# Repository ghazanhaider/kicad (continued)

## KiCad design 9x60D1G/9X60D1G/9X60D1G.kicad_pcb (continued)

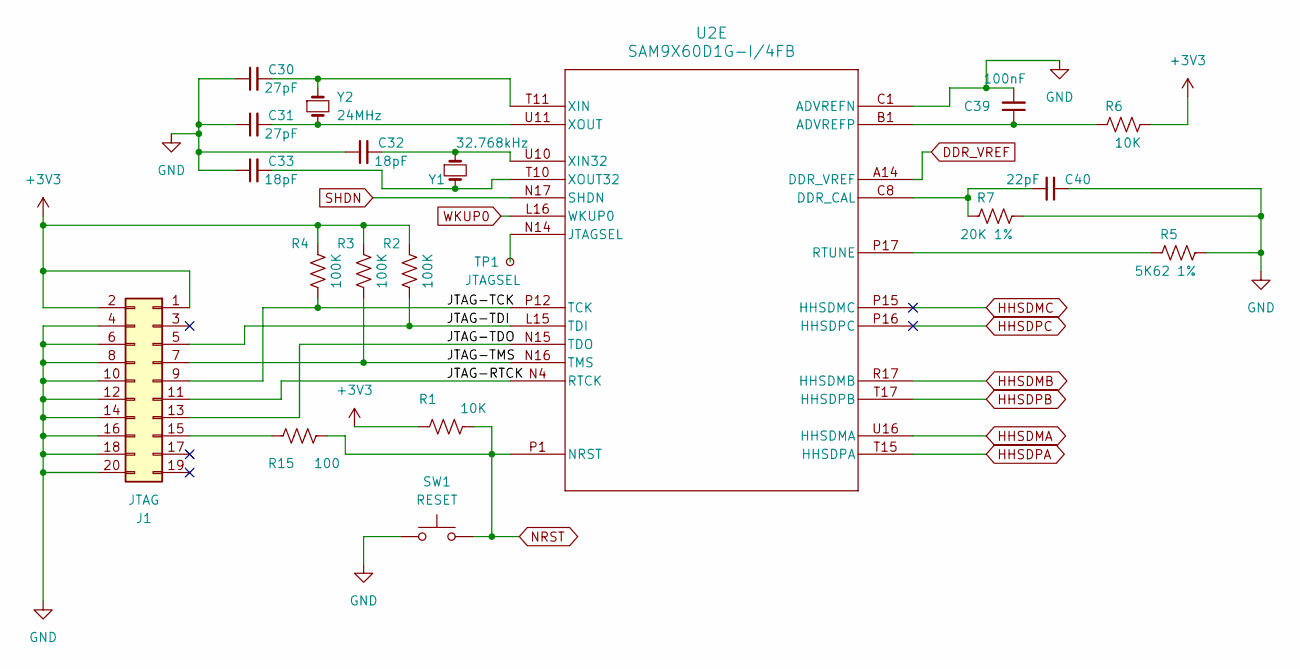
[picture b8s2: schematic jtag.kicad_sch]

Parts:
C30, C31: 27pF; C_0805_2012Metric
C32, C33: 18pF; C_0805_2012Metric
C39: 100nF; C_0805_2012Metric
C40: 22pF; C_0402_1005Metric
J1: JTAG; PinHeader_2x10_P2.54mm_Vertical
R1, R6: 10K; R_0805_2012Metric
R2, R3, R4: 100K; R_0805_2012Metric
R5: 5K62 1%; R_0402_1005Metric
R7: 20K 1%; R_0402_1005Metric
R15: 100; R_0805_2012Metric
SW1: RESET; SW_Push_1P1T_NO_6x6mm_H9.5mm
TP1: JTAGSEL; TestPoint_Pad_D1.0mm
U2: SAM9X60D1G-I/4FB; 233TFBGA_MCH
Y1: 32.768kHz; Crystal_SMD_3215-2Pin_3.2x1.5mm
Y2: 24MHz; Crystal_SMD_5032-2Pin_5.0x3.2mm

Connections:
+3V3: J1.1, J1.2, R1.1, R2.1, R3.1, R4.1, R6.2; also elsewhere on the board
/JTAG/JTAG-RTCK: J1.11, U2.N4 (RTCK)
/JTAG/JTAG-TCK: J1.9, R4.2, U2.P12 (TCK)
/JTAG/JTAG-TDI: J1.5, R2.2, U2.L15 (TDI)
/JTAG/JTAG-TDO: J1.13, U2.N15 (TDO)
/JTAG/JTAG-TMS: J1.7, R3.2, U2.N16 (TMS)
DDR_VREF: U2.A14 (DDR_VREF); also elsewhere on the board
GND: C30.1, C31.1, C32.1, C33.1, C39.2, C40.1, J1.4, J1.6, J1.8, J1.10, J1.12, J1.14, J1.16, J1.18, J1.20, R5.2, R7.2, SW1.1, U2.C1 (ADVREFN); also elsewhere on the board
HHSDMA: U2.U16 (HHSDMA); also elsewhere on the board
HHSDMB: U2.R17 (HHSDMB); also elsewhere on the board
HHSDMC: U2.P15 (HHSDMC)
HHSDPA: U2.T15 (HHSDPA); also elsewhere on the board
HHSDPB: U2.T17 (HHSDPB); also elsewhere on the board
HHSDPC: U2.P16 (HHSDPC)
NRST: R1.2, R15.2, SW1.2, U2.P1 (NRST); also elsewhere on the board
unnamed: J1.15, R15.1
unnamed: C39.1, R6.1, U2.B1 (ADVREFP)
unnamed: C40.2, R7.1, U2.C8 (DDR_CAL)
unnamed: TP1.1, U2.N14 (JTAGSEL)
unnamed: R5.1, U2.P17 (RTUNE)
unnamed: C32.2, U2.U10 (XIN32), Y1.1
unnamed: C30.2, U2.T11 (XIN), Y2.1
unnamed: C33.2, U2.T10 (XOUT32), Y1.2
unnamed: C31.2, U2.U11 (XOUT), Y2.2
SHDN: U2.N17 (SHDN); also elsewhere on the board
WKUP0: U2.L16 (WKUP0); also elsewhere on the board

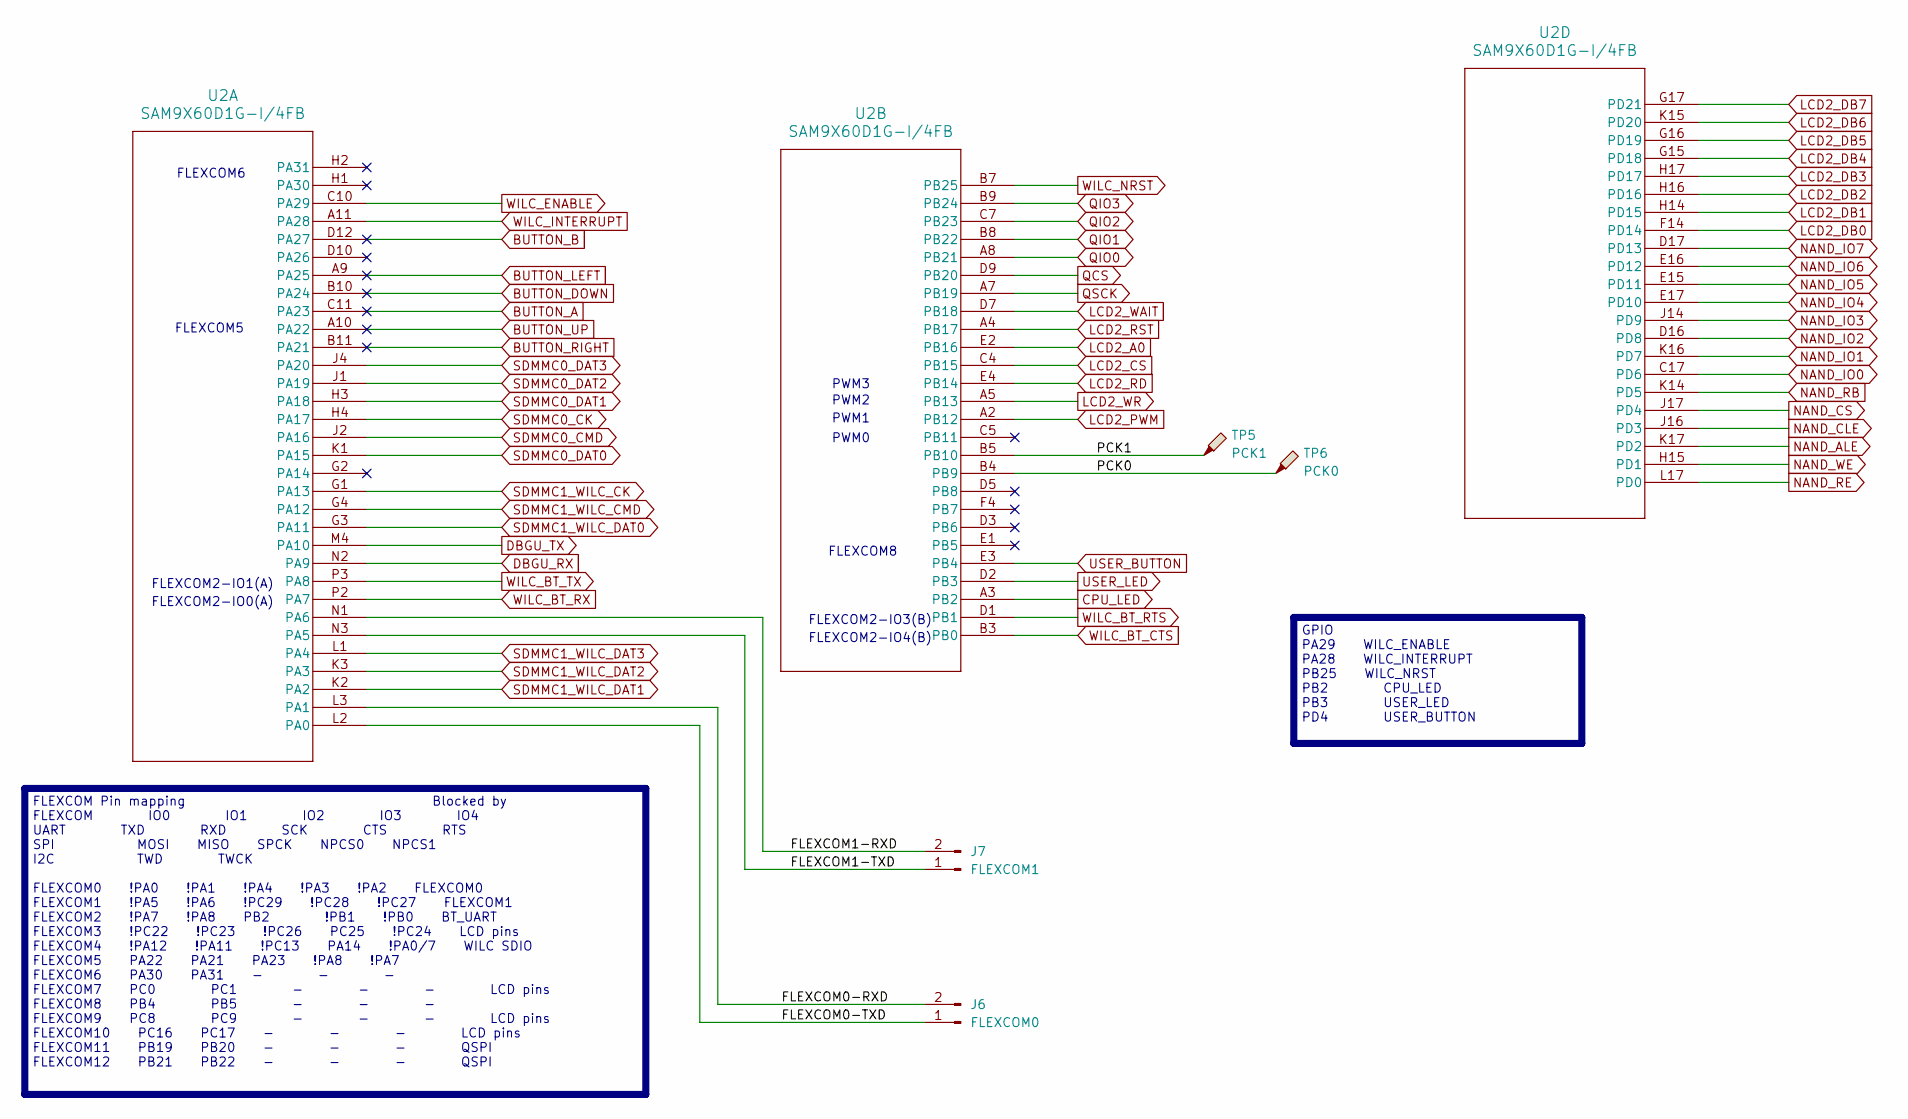
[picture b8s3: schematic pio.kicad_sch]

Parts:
J6: FLEXCOM0; PinHeader_1x02_P2.54mm_Vertical
J7: FLEXCOM1; PinHeader_1x02_P2.54mm_Vertical
TP5: PCK1; TestPoint_Pad_D1.0mm
TP6: PCK0; TestPoint_Pad_D1.0mm
U2: SAM9X60D1G-I/4FB; 233TFBGA_MCH

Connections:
/PIO breakout/FLEXCOM0-RXD: J6.2, U2.L3 (PA1)
/PIO breakout/FLEXCOM0-TXD: J6.1, U2.L2 (PA0)
/PIO breakout/FLEXCOM1-RXD: J7.2, U2.N1 (PA6)
/PIO breakout/FLEXCOM1-TXD: J7.1, U2.N3 (PA5)
/PIO breakout/PCK0: TP6.1, U2.B4 (PB9)
/PIO breakout/PCK1: TP5.1, U2.B5 (PB10)
BUTTON_A: U2.C11 (PA23); also elsewhere on the board
BUTTON_B: U2.D12 (PA27); also elsewhere on the board
BUTTON_DOWN: U2.B10 (PA24); also elsewhere on the board
BUTTON_LEFT: U2.A9 (PA25); also elsewhere on the board
BUTTON_RIGHT: U2.B11 (PA21); also elsewhere on the board
BUTTON_UP: U2.A10 (PA22); also elsewhere on the board
CPU_LED: U2.A3 (PB2); also elsewhere on the board
DBGU_RX: U2.N2 (PA9); also elsewhere on the board
DBGU_TX: U2.M4 (PA10); also elsewhere on the board
LCD2_A0: U2.E2 (PB16); also elsewhere on the board
LCD2_CS: U2.C4 (PB15); also elsewhere on the board
LCD2_DB0: U2.F14 (PD14); also elsewhere on the board
LCD2_DB1: U2.H14 (PD15); also elsewhere on the board
LCD2_DB2: U2.H16 (PD16); also elsewhere on the board
LCD2_DB3: U2.H17 (PD17); also elsewhere on the board
LCD2_DB4: U2.G15 (PD18); also elsewhere on the board
LCD2_DB5: U2.G16 (PD19); also elsewhere on the board
LCD2_DB6: U2.K15 (PD20); also elsewhere on the board
LCD2_DB7: U2.G17 (PD21); also elsewhere on the board
LCD2_PWM: U2.A2 (PB12); also elsewhere on the board
LCD2_RD: U2.E4 (PB14); also elsewhere on the board
LCD2_RST: U2.A4 (PB17); also elsewhere on the board
LCD2_WAIT: U2.D7 (PB18); also elsewhere on the board
LCD2_WR: U2.A5 (PB13); also elsewhere on the board
NAND_ALE: U2.K17 (PD2); also elsewhere on the board
NAND_CLE: U2.J16 (PD3); also elsewhere on the board
NAND_CS: U2.J17 (PD4); also elsewhere on the board
NAND_IO0: U2.C17 (PD6); also elsewhere on the board
NAND_IO1: U2.K16 (PD7); also elsewhere on the board
NAND_IO2: U2.D16 (PD8); also elsewhere on the board
NAND_IO3: U2.J14 (PD9); also elsewhere on the board
NAND_IO4: U2.E17 (PD10); also elsewhere on the board
NAND_IO5: U2.E15 (PD11); also elsewhere on the board
NAND_IO6: U2.E16 (PD12); also elsewhere on the board
NAND_IO7: U2.D17 (PD13); also elsewhere on the board
NAND_RB: U2.K14 (PD5); also elsewhere on the board
NAND_RE: U2.L17 (PD0); also elsewhere on the board
NAND_WE: U2.H15 (PD1); also elsewhere on the board
QCS: U2.D9 (PB20); also elsewhere on the board
QIO0: U2.A8 (PB21); also elsewhere on the board
QIO1: U2.B8 (PB22); also elsewhere on the board
QIO2: U2.C7 (PB23); also elsewhere on the board
QIO3: U2.B9 (PB24); also elsewhere on the board
QSCK: U2.A7 (PB19); also elsewhere on the board
SDMMC0_CK: U2.H4 (PA17); also elsewhere on the board
SDMMC0_CMD: U2.J2 (PA16); also elsewhere on the board
SDMMC0_DAT0: U2.K1 (PA15); also elsewhere on the board
SDMMC0_DAT1: U2.H3 (PA18); also elsewhere on the board
SDMMC0_DAT2: U2.J1 (PA19); also elsewhere on the board
SDMMC0_DAT3: U2.J4 (PA20); also elsewhere on the board
SDMMC1_WILC_CK: U2.G1 (PA13); also elsewhere on the board
SDMMC1_WILC_CMD: U2.G4 (PA12); also elsewhere on the board
SDMMC1_WILC_DAT0: U2.G3 (PA11); also elsewhere on the board
SDMMC1_WILC_DAT1: U2.K2 (PA2); also elsewhere on the board
SDMMC1_WILC_DAT2: U2.K3 (PA3); also elsewhere on the board
SDMMC1_WILC_DAT3: U2.L1 (PA4); also elsewhere on the board
USER_BUTTON: U2.E3 (PB4); also elsewhere on the board
USER_LED: U2.D2 (PB3); also elsewhere on the board
WILC_BT_CTS: U2.B3 (PB0); also elsewhere on the board
WILC_BT_RTS: U2.D1 (PB1); also elsewhere on the board
WILC_BT_RX: U2.P2 (PA7); also elsewhere on the board
WILC_BT_TX: U2.P3 (PA8); also elsewhere on the board
WILC_ENABLE: U2.C10 (PA29); also elsewhere on the board
WILC_INTERRUPT: U2.A11 (PA28); also elsewhere on the board
WILC_NRST: U2.B7 (PB25); also elsewhere on the board

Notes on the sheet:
GPIO PA29 WILC_ENABLE PA28 WILC_INTERRUPT PB25 WILC_NRST PB2 CPU_LED PB3 USER_LED PD4 USER_BUTTON
FLEXCOM Pin mapping Blocked by FLEXCOM IO0 IO1 IO2 IO3 IO4 UART TXD RXD SCK CTS RTS SPI MOSI MISO SPCK NPCS0 NPCS1 I2C TWD TWCK FLEXCOM0 !PA0 !PA1 !PA4 !PA3 !PA2 FLEXCOM0 FLEXCOM1 !PA5 !PA6 !PC29 !PC28 !PC27 FLEXCOM1 FLEXCOM2 !PA7 !PA8 PB2 !PB1 !PB0 BT_UART FLEXCOM3 !PC22 !PC23 !PC26 PC25 !PC24 LCD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
PWM3
FLEXCOM5
PWM0
FLEXCOM2-IO1(A)
FLEXCOM6
FLEXCOM2-IO4(B)
PWM1
FLEXCOM2-IO0(A)
PWM2
FLEXCOM2-IO3(B)
FLEXCOM8

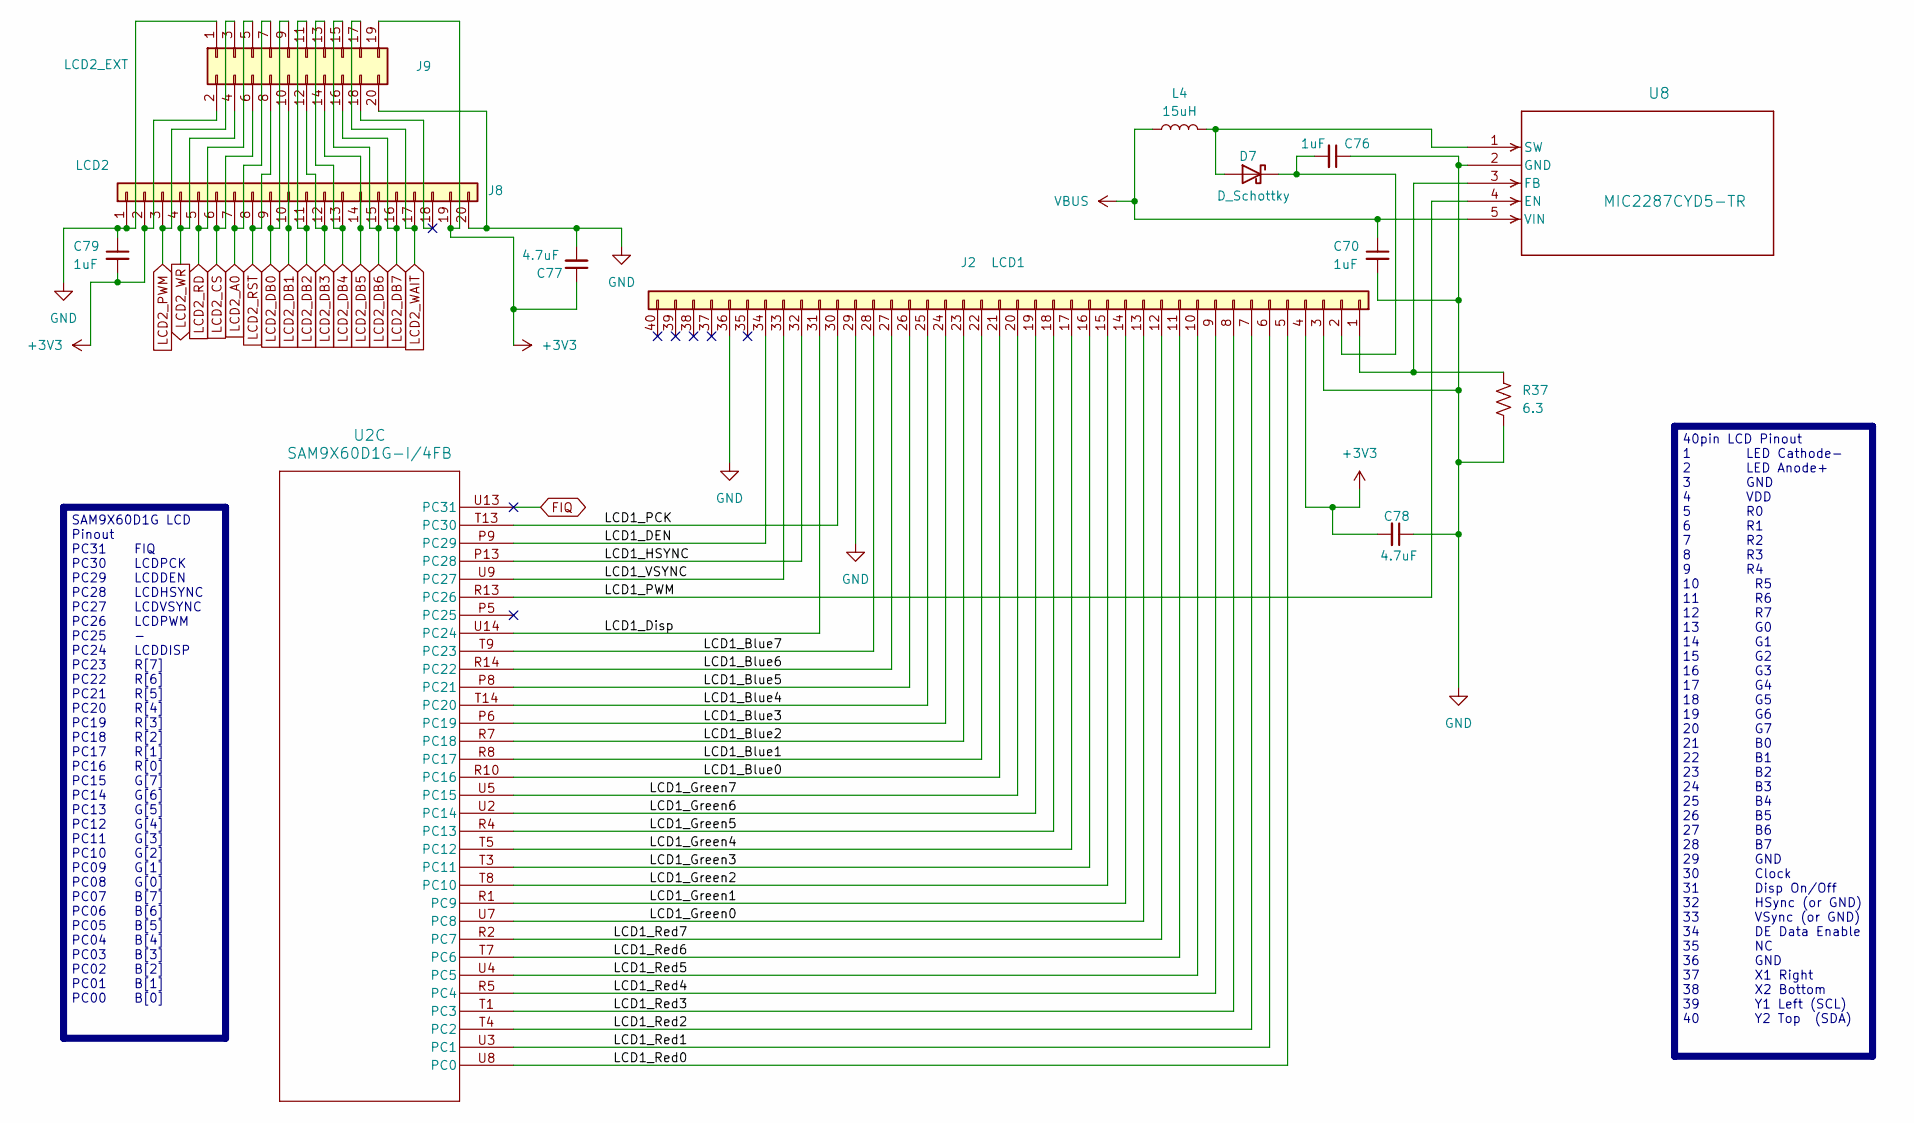
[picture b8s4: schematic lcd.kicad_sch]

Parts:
C70, C76, C79: 1uF; R_0805_2012Metric
C77: 4.7uF; C_0805_2012Metric
C78: 4.7uF; R_0805_2012Metric
D7: D_Schottky; D_0805_2012Metric
J2: LCD1; Hirose_FH12-40S-0.5SH_1x40-1MP_P0.50mm_Horizontal
J8: LCD2; TE_2-84952-0_1x20-1MP_P1.0mm_Horizontal
J9: LCD2_EXT; PinHeader_2x10_P2.54mm_Vertical
L4: 15uH; R_0805_2012Metric
R37: 6.3; R_0805_2012Metric
U2: SAM9X60D1G-I/4FB; 233TFBGA_MCH
U8: MIC2287CYD5-TR; TSOT-23-5_D5_MCH

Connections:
+3V3: C77.1, C78.2, C79.2, J2.4, J8.2, J8.19, J9.2, J9.19; also elsewhere on the board
/LCD/LCD1_Blue0: J2.21, U2.R10 (PC16)
/LCD/LCD1_Blue1: J2.22, U2.R8 (PC17)
/LCD/LCD1_Blue2: J2.23, U2.R7 (PC18)
/LCD/LCD1_Blue3: J2.24, U2.P6 (PC19)
/LCD/LCD1_Blue4: J2.25, U2.T14 (PC20)
/LCD/LCD1_Blue5: J2.26, U2.P8 (PC21)
/LCD/LCD1_Blue6: J2.27, U2.R14 (PC22)
/LCD/LCD1_Blue7: J2.28, U2.T9 (PC23)
/LCD/LCD1_DEN: J2.34, U2.P9 (PC29)
/LCD/LCD1_Disp: J2.31, U2.U14 (PC24)
/LCD/LCD1_Green0: J2.13, U2.U7 (PC8)
/LCD/LCD1_Green1: J2.14, U2.R1 (PC9)
/LCD/LCD1_Green2: J2.15, U2.T8 (PC10)
/LCD/LCD1_Green3: J2.16, U2.T3 (PC11)
/LCD/LCD1_Green4: J2.17, U2.T5 (PC12)
/LCD/LCD1_Green5: J2.18, U2.R4 (PC13)
/LCD/LCD1_Green6: J2.19, U2.U2 (PC14)
/LCD/LCD1_Green7: J2.20, U2.U5 (PC15)
/LCD/LCD1_HSYNC: J2.32, U2.P13 (PC28)
/LCD/LCD1_PCK: J2.30, U2.T13 (PC30)
/LCD/LCD1_PWM: U2.R13 (PC26), U8.4 (EN)
/LCD/LCD1_Red0: J2.5, U2.U8 (PC0)
/LCD/LCD1_Red1: J2.6, U2.U3 (PC1)
/LCD/LCD1_Red2: J2.7, U2.T4 (PC2)
/LCD/LCD1_Red3: J2.8, U2.T1 (PC3)
/LCD/LCD1_Red4: J2.9, U2.R5 (PC4)
/LCD/LCD1_Red5: J2.10, U2.U4 (PC5)
/LCD/LCD1_Red6: J2.11, U2.T7 (PC6)
/LCD/LCD1_Red7: J2.12, U2.R2 (PC7)
/LCD/LCD1_VSYNC: J2.33, U2.U9 (PC27)
FIQ: U2.U13 (PC31)
GND: C70.2, C76.1, C77.2, C78.1, C79.1, J2.3, J2.29, J2.36, J8.1, J8.20, J9.1, J9.20, R37.2, U8.2 (GND); also elsewhere on the board
LCD2_A0: J8.7, J9.7; also elsewhere on the board
LCD2_CS: J8.6, J9.6; also elsewhere on the board
LCD2_DB0: J8.9, J9.9; also elsewhere on the board
LCD2_DB1: J8.10, J9.10; also elsewhere on the board
LCD2_DB2: J8.11, J9.11; also elsewhere on the board
LCD2_DB3: J8.12, J9.12; also elsewhere on the board
LCD2_DB4: J8.13, J9.13; also elsewhere on the board
LCD2_DB5: J8.14, J9.14; also elsewhere on the board
LCD2_DB6: J8.15, J9.15; also elsewhere on the board
LCD2_DB7: J8.16, J9.16; also elsewhere on the board
LCD2_PWM: J8.3, J9.3; also elsewhere on the board
LCD2_RD: J8.5, J9.5; also elsewhere on the board
LCD2_RST: J8.8, J9.8; also elsewhere on the board
LCD2_WAIT: J8.17, J9.17; also elsewhere on the board
LCD2_WR: J8.4, J9.4; also elsewhere on the board
unnamed: D7.2 (A), L4.2, U8.1 (SW)
unnamed: C76.2, D7.1 (K), J2.2
unnamed: J2.1, R37.1, U8.3 (FB)
VBUS: C70.1, L4.1, U8.5 (VIN); also elsewhere on the board

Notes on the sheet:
SAM9X60D1G LCD Pinout PC31 FIQ PC30 LCDPCK PC29 LCDDEN PC28 LCDHSYNC PC27 LCDVSYNC PC26 LCDPWM PC25 - PC24 LCDDISP PC23 R[7] PC22 R[6] PC21 R[5] PC20 R[4] PC19 R[3] PC18 R[2] PC17 R[1] PC16 R[0] PC15 G[7] PC14 G[6] PC13 G[5] PC12 G[4] PC11 G[3] PC10 G[2] PC09 G[1] PC08 G[0] PC07 B[7] PC06 B[6] PC05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
40pin LCD Pinout 1 LED Cathode- 2 LED Anode+ 3 GND 4 VDD 5 R0 6 R1 7 R2 8 R3 9 R4 10 R5 11 R6 12 R7 13 G0 14 G1 15 G2 16 G3 17 G4 18 G5 19 G6 20 G7 21 B0 22 B1 23 B2 24 B3 25 B4 26 B5 27 B6 28 B7 29 GND 30 Clock 31 Disp On/Off 32 HSync (or GND) 33 VSync (or GND) 34 DE Data Enable 35 NC 36 GND 37 X1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

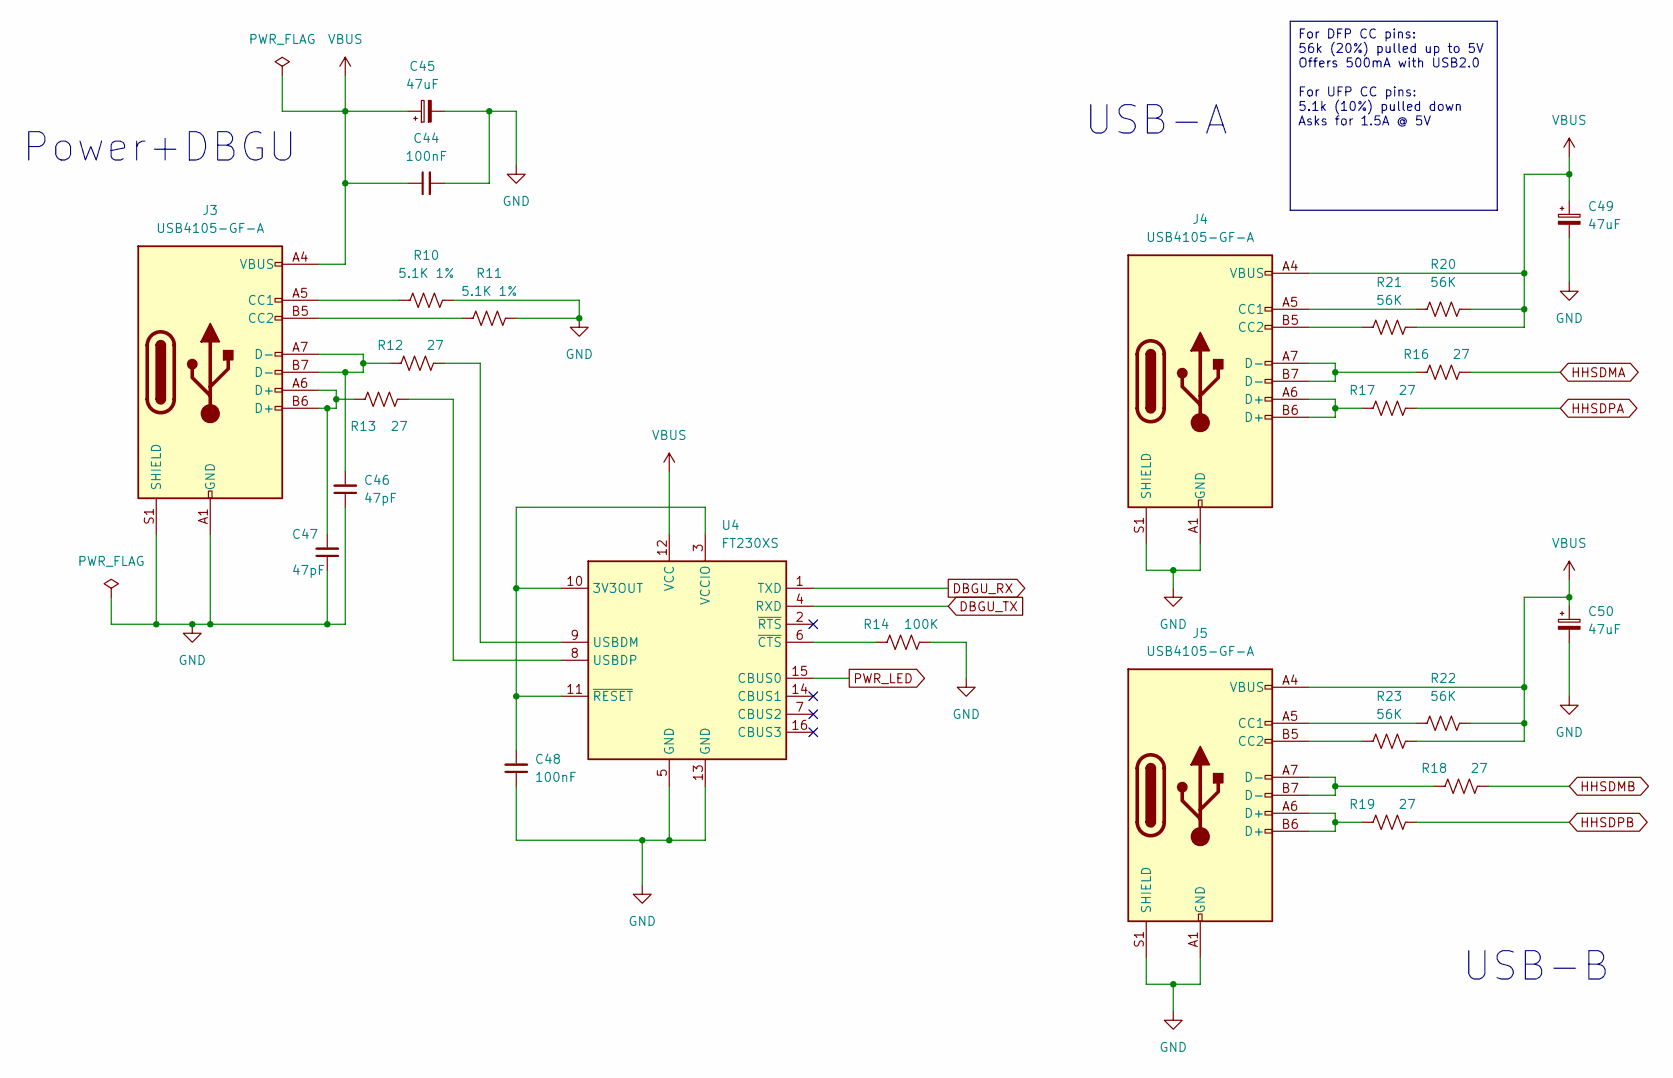
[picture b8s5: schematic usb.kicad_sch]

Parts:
C44, C48: 100nF; C_0805_2012Metric
C45, C49, C50: 47uF; C_0805_2012Metric
C46, C47: 47pF; C_0805_2012Metric
J3, J4, J5: USB4105-GF-A; USB_C_Receptacle_GCT_USB4105-xx-A_16P_TopMnt_Horizontal
R10, R11: 5.1K 1%; R_0805_2012Metric
R12, R13, R16, R17, R18, R19: 27; R_0805_2012Metric
R14: 100K; R_0805_2012Metric
R20, R21, R22, R23: 56K; R_0805_2012Metric
U4: FT230XS; SSOP-16_3.9x4.9mm_P0.635mm

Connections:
DBGU_RX: U4.1 (TXD); also elsewhere on the board
DBGU_TX: U4.4 (RXD); also elsewhere on the board
GND: C44.2, C45.2, C46.1, C47.1, C48.1, C49.2, C50.2, J3.A1 (GND), J3.A12 (GND), J3.B1 (GND), J3.B12 (GND), J3.S1 (SHIELD), J4.A1 (GND), J4.A12 (GND), J4.B1 (GND), J4.B12 (GND), J4.S1 (SHIELD), J5.A1 (GND), J5.A12 (GND), J5.B1 (GND), J5.B12 (GND), J5.S1 (SHIELD), R10.2, R11.2, R14.2, U4.5 (GND), U4.13 (GND); also elsewhere on the board
HHSDMA: R16.2; also elsewhere on the board
HHSDMB: R18.2; also elsewhere on the board
HHSDPA: R17.2; also elsewhere on the board
HHSDPB: R19.2; also elsewhere on the board
unnamed: C46.2, J3.A7 (D-), J3.B7 (D-), R12.1
unnamed: C47.2, J3.A6 (D+), J3.B6 (D+), R13.1
unnamed: J3.A5 (CC1), R10.1
unnamed: J3.B5 (CC2), R11.1
unnamed: J4.A5 (CC1), R20.1
unnamed: J4.B5 (CC2), R21.1
unnamed: J4.A6 (D+), J4.B6 (D+), R17.1
unnamed: J4.A7 (D-), J4.B7 (D-), R16.1
unnamed: J5.A5 (CC1), R22.1
unnamed: J5.B5 (CC2), R23.1
unnamed: J5.A6 (D+), J5.B6 (D+), R19.1
unnamed: J5.A7 (D-), J5.B7 (D-), R18.1
unnamed: C48.2, U4.3 (VCCIO), U4.10 (3V3OUT), U4.11 (~RESET)
unnamed: R12.2, U4.9 (USBDM)
unnamed: R13.2, U4.8 (USBDP)
unnamed: R14.1, U4.6 (~CTS)
PWR_LED: U4.15 (CBUS0); also elsewhere on the board
VBUS: C44.1, C45.1, C49.1, C50.1, J3.A4 (VBUS), J3.A9 (VBUS), J3.B4 (VBUS), J3.B9 (VBUS), J4.A4 (VBUS), J4.A9 (VBUS), J4.B4 (VBUS), J4.B9 (VBUS), J5.A4 (VBUS), J5.A9 (VBUS), J5.B4 (VBUS), J5.B9 (VBUS), R20.2, R21.2, R22.2, R23.2, U4.12 (VCC); also elsewhere on the board

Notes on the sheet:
For DFP CC pins: 56k (20%) pulled up to 5V Offers 500mA with USB2.0 For UFP CC pins: 5.1k (10%) pulled down Asks for 1.5A @ 5V
Power+DBGU
USB-A
USB-B

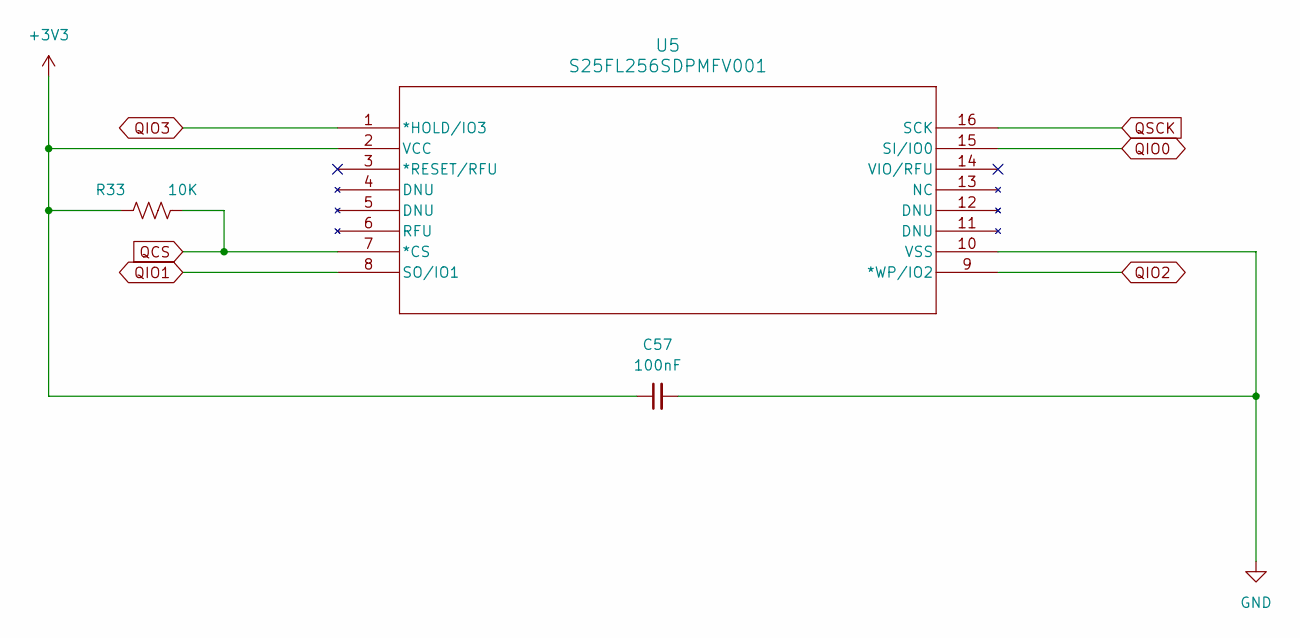
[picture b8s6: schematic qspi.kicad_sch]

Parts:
C57: 100nF; C_0805_2012Metric
R33: 10K; R_0805_2012Metric
U5: S25FL256SDPMFV001; SO3016_SPA

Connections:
+3V3: C57.1, R33.1, U5.2 (VCC); also elsewhere on the board
GND: C57.2, U5.10 (VSS); also elsewhere on the board
QCS: R33.2, U5.7 (*CS); also elsewhere on the board
QIO0: U5.15 (SI/IO0); also elsewhere on the board
QIO1: U5.8 (SO/IO1); also elsewhere on the board
QIO2: U5.9 (*WP/IO2); also elsewhere on the board
QIO3: U5.1 (*HOLD/IO3); also elsewhere on the board
QSCK: U5.16 (SCK); also elsewhere on the board

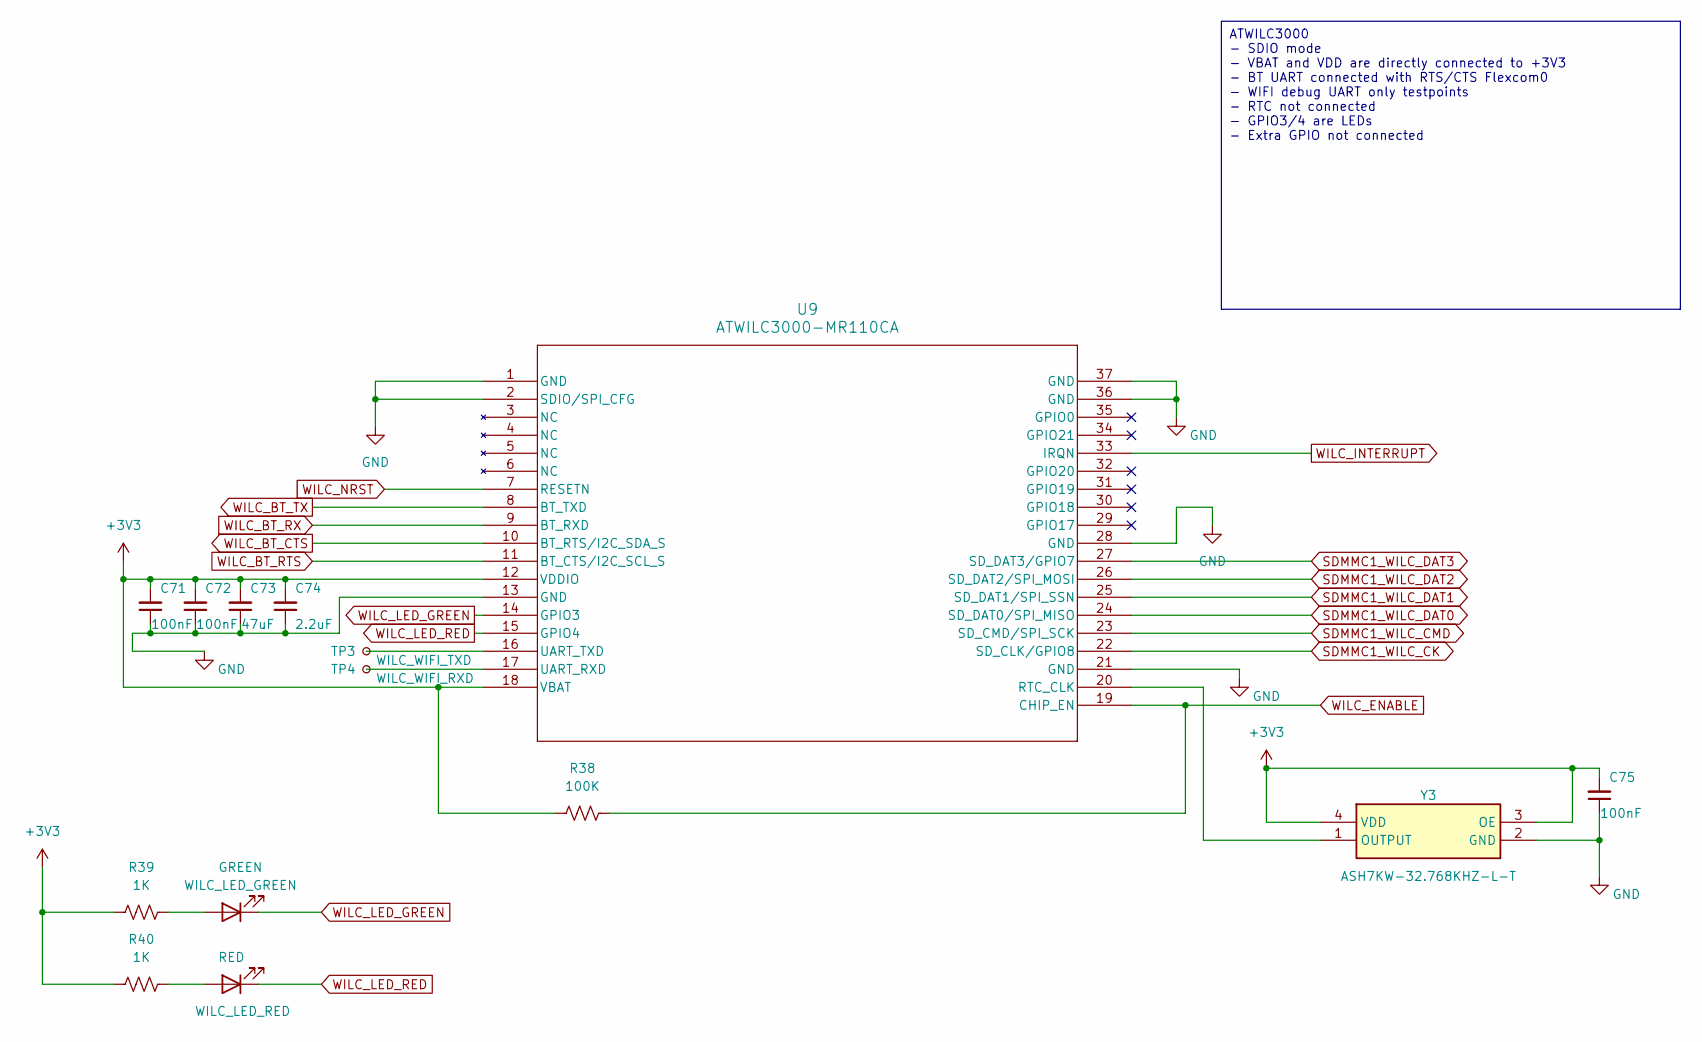
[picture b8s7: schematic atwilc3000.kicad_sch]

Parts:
C71, C72, C75: 100nF; C_0805_2012Metric
C73: 47uF; C_0805_2012Metric
C74: 2.2uF; C_0805_2012Metric
D4: WILC_LED_GREEN; LED_0805_2012Metric
D5: WILC_LED_RED; LED_0805_2012Metric
R38: 100K; R_0805_2012Metric
R39, R40: 1K; R_0805_2012Metric
TP3: WILC_WIFI_TXD; TestPoint_Pad_D1.0mm
TP4: WILC_WIFI_RXD; TestPoint_Pad_D1.0mm
U9: ATWILC3000-MR110CA; ATWILC3000-MR110CA_MCH
Y3: ASH7KW-32.768KHZ-L-T; ASH7KW32768kHzLT; Mouser Part Number 815-ASH7KW-32.7-L-T

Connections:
+3V3: C71.2, C72.2, C73.2, C74.2, C75.2, R38.1, R39.1, R40.1, U9.12 (VDDIO), U9.18 (VBAT), Y3.3 (OE), Y3.4 (VDD); also elsewhere on the board
GND: C71.1, C72.1, C73.1, C74.1, C75.1, U9.1 (GND), U9.2 (SDIO/SPI_CFG), U9.13 (GND), U9.21 (GND), U9.28 (GND), U9.36 (GND), U9.37 (GND), Y3.2 (GND); also elsewhere on the board
unnamed: D4.2 (A), R39.2
unnamed: D5.2 (A), R40.2
unnamed: U9.20 (RTC_CLK), Y3.1 (OUTPUT)
unnamed: TP4.1, U9.17 (UART_RXD)
unnamed: TP3.1, U9.16 (UART_TXD)
SDMMC1_WILC_CK: U9.22 (SD_CLK/GPIO8); also elsewhere on the board
SDMMC1_WILC_CMD: U9.23 (SD_CMD/SPI_SCK); also elsewhere on the board
SDMMC1_WILC_DAT0: U9.24 (SD_DAT0/SPI_MISO); also elsewhere on the board
SDMMC1_WILC_DAT1: U9.25 (SD_DAT1/SPI_SSN); also elsewhere on the board
SDMMC1_WILC_DAT2: U9.26 (SD_DAT2/SPI_MOSI); also elsewhere on the board
SDMMC1_WILC_DAT3: U9.27 (SD_DAT3/GPIO7); also elsewhere on the board
WILC_BT_CTS: U9.10 (BT_RTS/I2C_SDA_S); also elsewhere on the board
WILC_BT_RTS: U9.11 (BT_CTS/I2C_SCL_S); also elsewhere on the board
WILC_BT_RX: U9.9 (BT_RXD); also elsewhere on the board
WILC_BT_TX: U9.8 (BT_TXD); also elsewhere on the board
WILC_ENABLE: R38.2, U9.19 (CHIP_EN); also elsewhere on the board
WILC_INTERRUPT: U9.33 (IRQN); also elsewhere on the board
WILC_LED_GREEN: D4.1 (K), U9.14 (GPIO3)
WILC_LED_RED: D5.1 (K), U9.15 (GPIO4)
WILC_NRST: U9.7 (RESETN); also elsewhere on the board

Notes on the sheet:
ATWILC3000 - SDIO mode - VBAT and VDD are directly connected to +3V3 - BT UART connected with RTS/CTS Flexcom0 - WIFI debug UART only testpoints - RTC not connected - GPIO3/4 are LEDs - Extra GPIO not connected

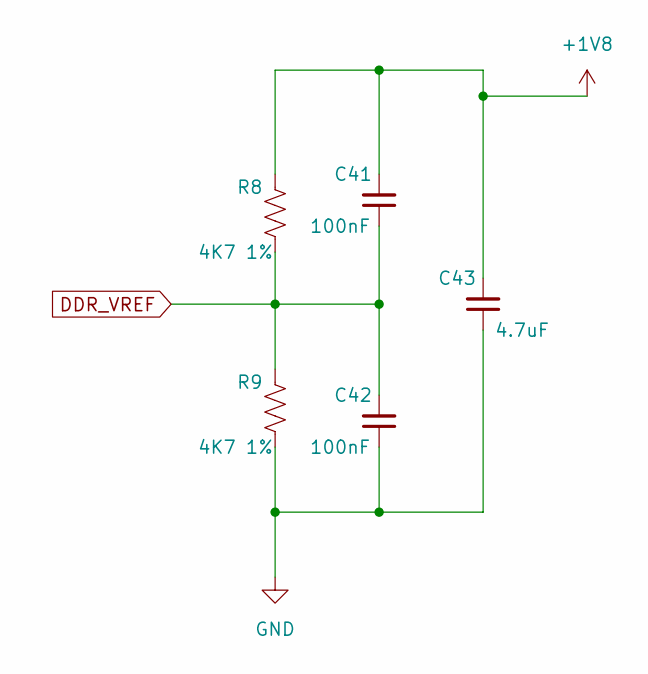
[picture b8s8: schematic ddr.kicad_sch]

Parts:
C41, C42: 100nF; C_0402_1005Metric
C43: 4.7uF; C_0402_1005Metric
R8, R9: 4K7 1%; R_0402_1005Metric

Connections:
+1V8: C41.2, C43.2, R8.1; also elsewhere on the board
DDR_VREF: C41.1, C42.2, R8.2, R9.1; also elsewhere on the board
GND: C42.1, C43.1, R9.2; also elsewhere on the board

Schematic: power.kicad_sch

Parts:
C1, C2, C3, C4, C5, C6, C7, C8, C9, C10, C11, C12, C13, C14, C15, C16, C17, C18, C19, C20, C21, C22, C23, C24, C25, C26, C27, C28, C29, C34: 100nF; C_0402_1005Metric
C35, C36, C37, C53, C54: 4.7uF; C_0805_2012Metric
C38, C55, C56: 22uF; C_0805_2012Metric
L1, L2, L3: 1.5uH; L_0805_2012Metric
R27: 1K; R_0805_2012Metric
R28: 10K; R_0805_2012Metric
R29: 270K 1%; R_0805_2012Metric
R30: 100K 1%; R_0805_2012Metric
TP2: LDO_OUT; TestPoint_Pad_D1.0mm
U2: SAM9X60D1G-I/4FB; 233TFBGA_MCH
U3: MCP16501TA-E/RMB; VQFN24_RMB_MCH

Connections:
+1V8: C4.2, C5.2, C6.2, C7.2, C8.2, C9.2, C10.2, C11.2, C12.2, C13.2, C15.2, C19.2, C20.2, C21.2, C55.2, L2.1, U2.A16 (DDRM_VDD), U2.B15 (DDRM_VDD), U2.B17 (DDRM_VDD), U2.C14 (DDRM_VDD), U2.C16 (DDRM_VDD), U2.D11 (VDDIOM), U2.D13 (DDRM_VDD), U2.D15 (DDRM_VDD), U2.E11 (DDRM_VDD), U2.E12 (DDRM_VDD), U2.E14 (VDDIOM), U2.F13 (DDRM_VDD), U2.G13 (DDRM_VDD), U2.G14 (VDDIOM), U3.6 (OUT2); also elsewhere on the board
+1V15: C23.2, C24.2, C25.2, C26.2, C27.2, C56.2, L3.1, U2.D6 (VDDCORE), U2.D8 (VDDCORE), U2.G5 (VDDCORE), U2.L6 (VDDCORE), U2.M7 (VDDCORE), U3.13 (OUT3)
+3V3: C1.2, C2.2, C3.2, C14.2, C16.2, C17.2, C18.2, C22.2, C28.2, C29.2, C38.1, L1.2, R28.2, U2.C2 (VDDANA), U2.C6 (VDDQSPI), U2.F5 (VDDIOP0), U2.K4 (VDDIOP0), U2.L4 (VDDIOP0), U2.M3 (VDDIOP1), U2.M15 (VDDNF), U2.N11 (VDDIN33), U2.R6 (VDDBU), U2.R12 (VDDIN33), U3.1 (OUT1); also elsewhere on the board
/Power/VDDOUT25: C34.2, U2.P11 (VDDOUT25)
GND: C1.1, C2.1, C3.1, C4.1, C5.1, C6.1, C7.1, C8.1, C9.1, C10.1, C11.1, C12.1, C13.1, C14.1, C15.1, C16.1, C17.1, C18.1, C19.1, C20.1, C21.1, C22.1, C23.1, C24.1, C25.1, C26.1, C27.1, C28.1, C29.1, C34.1, C35.2, C36.1, C37.2, C38.2, C53.1, C54.1, C55.1, C56.1, R30.2, U2.A1 (GND), U2.A13 (GND), U2.A15 (GND), U2.A17 (DDR_VSS), U2.B2 (GND), U2.B13 (GND), U2.B14 (GND), U2.B16 (DDR_VSS), U2.C3 (GNDANA), U2.C9 (GND), U2.C12 (DDR_VSS), U2.C13 (GND), U2.C15 (DDR_VSS), U2.D4 (GND), U2.D14 (DDR_VSS), U2.E5 (GND), U2.E6 (GND), U2.E7 (GND), U2.E13 (DDR_VSS), U2.F3 (GND), U2.F6 (GND), U2.F7 (GND), U2.F11 (DDR_VSS), U2.F12 (DDR_VSS), U2.F15 (DDR_VSS), U2.G6 (GND), U2.G12 (DDR_VSS), U2.H8 (GND), U2.H9 (GND), U2.H10 (GND), U2.J3 (GND), U2.J8 (GND), U2.J9 (GND), U2.J10 (GND), U2.J15 (GND), U2.K8 (GND), U2.K9 (GND), U2.K10 (GND), U2.L5 (GND), U2.L12 (GND), U2.L13 (GND), U2.L14 (GND), U2.M5 (GND), U2.M6 (GND), U2.M11 (GND), U2.M12 (GND), U2.M13 (GND), U2.M14 (GND), U2.N5 (GND), U2.N6 (GND), U2.N7 (GNDIN33), U2.N12 (GND), U2.N13 (GND), U2.P4 (GND), U2.P7 (GNDIN33), U2.P10 (GND), U2.P14 (GND), U2.R3 (GND), U2.R9 (GND), U2.R11 (GND), U2.R15 (GND), U2.R16 (GND), U2.T2 (GND), U2.T16 (GND), U2.U1 (GND), U2.U15 (GND), U2.U17 (GND), U3.4 (LPM), U3.9 (PGND2), U3.10 (PGND3), U3.16 (SGND), U3.22 (PGND1), U3.25 (GND); also elsewhere on the board
NRST: U3.2 (nRSTO); also elsewhere on the board
unnamed: R29.1, R30.1, U3.19 (LFB)
unnamed: C54.2, R29.2, TP2.1, U3.18 (LOUT)
unnamed: R27.2, U3.3 (PWRHLD)
unnamed: L1.1, U3.23 (SW1)
unnamed: L2.2, U3.8 (SW2)
unnamed: L3.2, U3.11 (SW3)
SHDN: R27.1; also elsewhere on the board
START: U3.14 (nSTRT); also elsewhere on the board
VBUS: C35.1, C36.2, C37.1, C53.2, U3.7 (PVIN2), U3.12 (PVIN3), U3.17 (VIN), U3.20 (SELV2), U3.21 (LEN), U3.24 (PVIN1); also elsewhere on the board
WKUP0: R28.1, U3.5 (nSTRTO); also elsewhere on the board

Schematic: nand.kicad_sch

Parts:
C68, C69: 100nF; C_0805_2012Metric
JP1: NANDBOOT; SolderJumper-2_P1.3mm_Bridged_RoundedPad1.0x1.5mm
R34, R35, R36: 100K; R_0805_2012Metric
U7: MT29F4G08ABAFAWP-IT:F; TSOPI-48_MRN

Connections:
+3V3: C68.2, C69.1, R34.1, R35.1, R36.1, U7.12 (VCC), U7.37 (VCC); also elsewhere on the board
/NAND/NAND_CE: JP1.2 (B), R35.2, U7.9 (CE#)
GND: C68.1, C69.2, U7.13 (VSS), U7.36 (VSS), U7.38 (PRE/VSS); also elsewhere on the board
NAND_ALE: U7.17 (ALE); also elsewhere on the board
NAND_CLE: U7.16 (CLE); also elsewhere on the board
NAND_CS: JP1.1 (A); also elsewhere on the board
NAND_IO0: U7.29 (I/O0); also elsewhere on the board
NAND_IO1: U7.30 (I/O1); also elsewhere on the board
NAND_IO2: U7.31 (I/O2); also elsewhere on the board
NAND_IO3: U7.32 (I/O3); also elsewhere on the board
NAND_IO4: U7.41 (I/O4); also elsewhere on the board
NAND_IO5: U7.42 (I/O5); also elsewhere on the board
NAND_IO6: U7.43 (I/O6); also elsewhere on the board
NAND_IO7: U7.44 (I/O7); also elsewhere on the board
NAND_RB: R34.2, U7.7 (R/B#); also elsewhere on the board
NAND_RE: U7.8 (RE#); also elsewhere on the board
NAND_WE: U7.18 (WE#); also elsewhere on the board
unnamed: R36.2, U7.19 (WP#)

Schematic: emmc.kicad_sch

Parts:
C58, C59, C60, C61, C62, C63, C64, C65, C66, C67: 2.2uF; C_0402_1005Metric
U6: THGBMTG5D1LBAIL; BGA153_THGBMJ_KIO

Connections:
+3V3: C58.2, C59.2, C60.1, C61.1, C62.2, C63.2, C64.2, C65.1, C66.1, C67.1, U6.C2 (VDDI), U6.C6 (VCCQ), U6.E6 (VCC), U6.F5 (VCC), U6.J10 (VCC), U6.K9 (VCC), U6.M4 (VCCQ), U6.N4 (VCCQ), U6.P3 (VCCQ), U6.P5 (VCCQ); also elsewhere on the board
GND: C58.1, C59.1, C60.2, C61.2, C62.1, C63.1, C64.1, C65.2, C66.2, C67.2, U6.A6 (VSS), U6.C4 (VSSQ), U6.E7 (VSS), U6.G5 (VSS), U6.H10 (VSS), U6.J5 (VSS), U6.K8 (VSS), U6.N2 (VSSQ), U6.N5 (VSSQ), U6.P4 (VSSQ), U6.P6 (VSSQ); also elsewhere on the board
SDMMC0_CK: U6.M6 (CLK); also elsewhere on the board
SDMMC0_CMD: U6.M5 (CMD); also elsewhere on the board
SDMMC0_DAT0: U6.A3 (DAT0); also elsewhere on the board
SDMMC0_DAT1: U6.A4 (DAT1); also elsewhere on the board
SDMMC0_DAT2: U6.A5 (DAT2); also elsewhere on the board
SDMMC0_DAT3: U6.B2 (DAT3); also elsewhere on the board

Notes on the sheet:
Hard to reach ball
